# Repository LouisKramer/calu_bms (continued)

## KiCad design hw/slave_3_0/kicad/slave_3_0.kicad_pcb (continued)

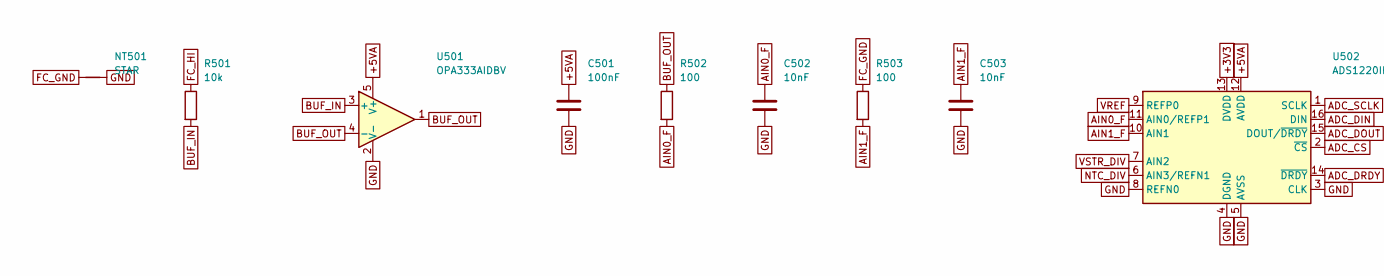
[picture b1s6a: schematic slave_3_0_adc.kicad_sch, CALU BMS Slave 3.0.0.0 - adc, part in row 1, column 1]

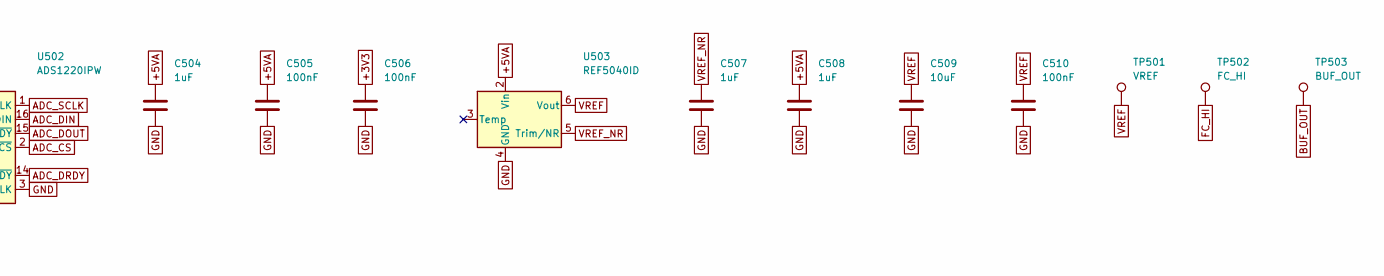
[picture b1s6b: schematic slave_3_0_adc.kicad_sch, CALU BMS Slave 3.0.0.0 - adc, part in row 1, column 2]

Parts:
C501, C505, C506: 100nF; C_0603_1608Metric
C502, C503: 10nF; C_0603_1608Metric
C504, C507, C508: 1uF; C_0603_1608Metric
C509: 10uF; C_0805_2012Metric
C510: 100nF; C_0805_2012Metric
NT501: STAR; NetTie-2_SMD_Pad0.5mm
R501: 10k; R_0603_1608Metric
R502, R503: 100; R_0603_1608Metric
TP501: VREF; TestPoint_Pad_D1.0mm
TP502: FC_HI; TestPoint_Pad_D1.0mm
TP503: BUF_OUT; TestPoint_Pad_D1.0mm
U501: OPA333AIDBV; SOT-23-5
U502: ADS1220IPW; TSSOP-16_4.4x5mm_P0.65mm
U503: REF5040ID; SOIC-8_3.9x4.9mm_P1.27mm

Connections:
+3V3: C506.1, U502.13 (DVDD); also elsewhere on the board
+5VA: C501.1, C504.1, C505.1, C508.1, U501.5 (V+), U502.12 (AVDD), U503.2 (Vin); also elsewhere on the board
ADC_CS: U502.2 (~CS); also elsewhere on the board
ADC_DIN: U502.16 (DIN); also elsewhere on the board
ADC_DOUT: U502.15 (DOUT/~DRDY); also elsewhere on the board
ADC_DRDY: U502.14 (~DRDY); also elsewhere on the board
ADC_SCLK: U502.1 (SCLK); also elsewhere on the board
AIN0_F: C502.1, R502.2, U502.11 (AIN0/REFP1)
AIN1_F: C503.1, R503.2, U502.10 (AIN1)
BUF_IN: R501.2, U501.3 (+)
BUF_OUT: R502.1, TP503.1 (1_1), U501.1, U501.4 (-)
FC_GND: NT501.1, R503.1; also elsewhere on the board
FC_HI: R501.1, TP502.1 (1_1); also elsewhere on the board
GND: C501.2, C502.2, C503.2, C504.2, C505.2, C506.2, C507.2, C508.2, C509.2, C510.2, NT501.2, U501.2 (V-), U502.3 (CLK), U502.4 (DGND), U502.5 (AVSS), U502.8 (REFN0), U503.4 (GND); also elsewhere on the board
NTC_DIV: U502.6 (AIN3/REFN1); also elsewhere on the board
VREF: C509.1, C510.1, TP501.1 (1_1), U502.9 (REFP0), U503.6 (Vout); also elsewhere on the board
VREF_NR: C507.1, U503.5 (Trim/NR)
VSTR_DIV: U502.7 (AIN2); also elsewhere on the board

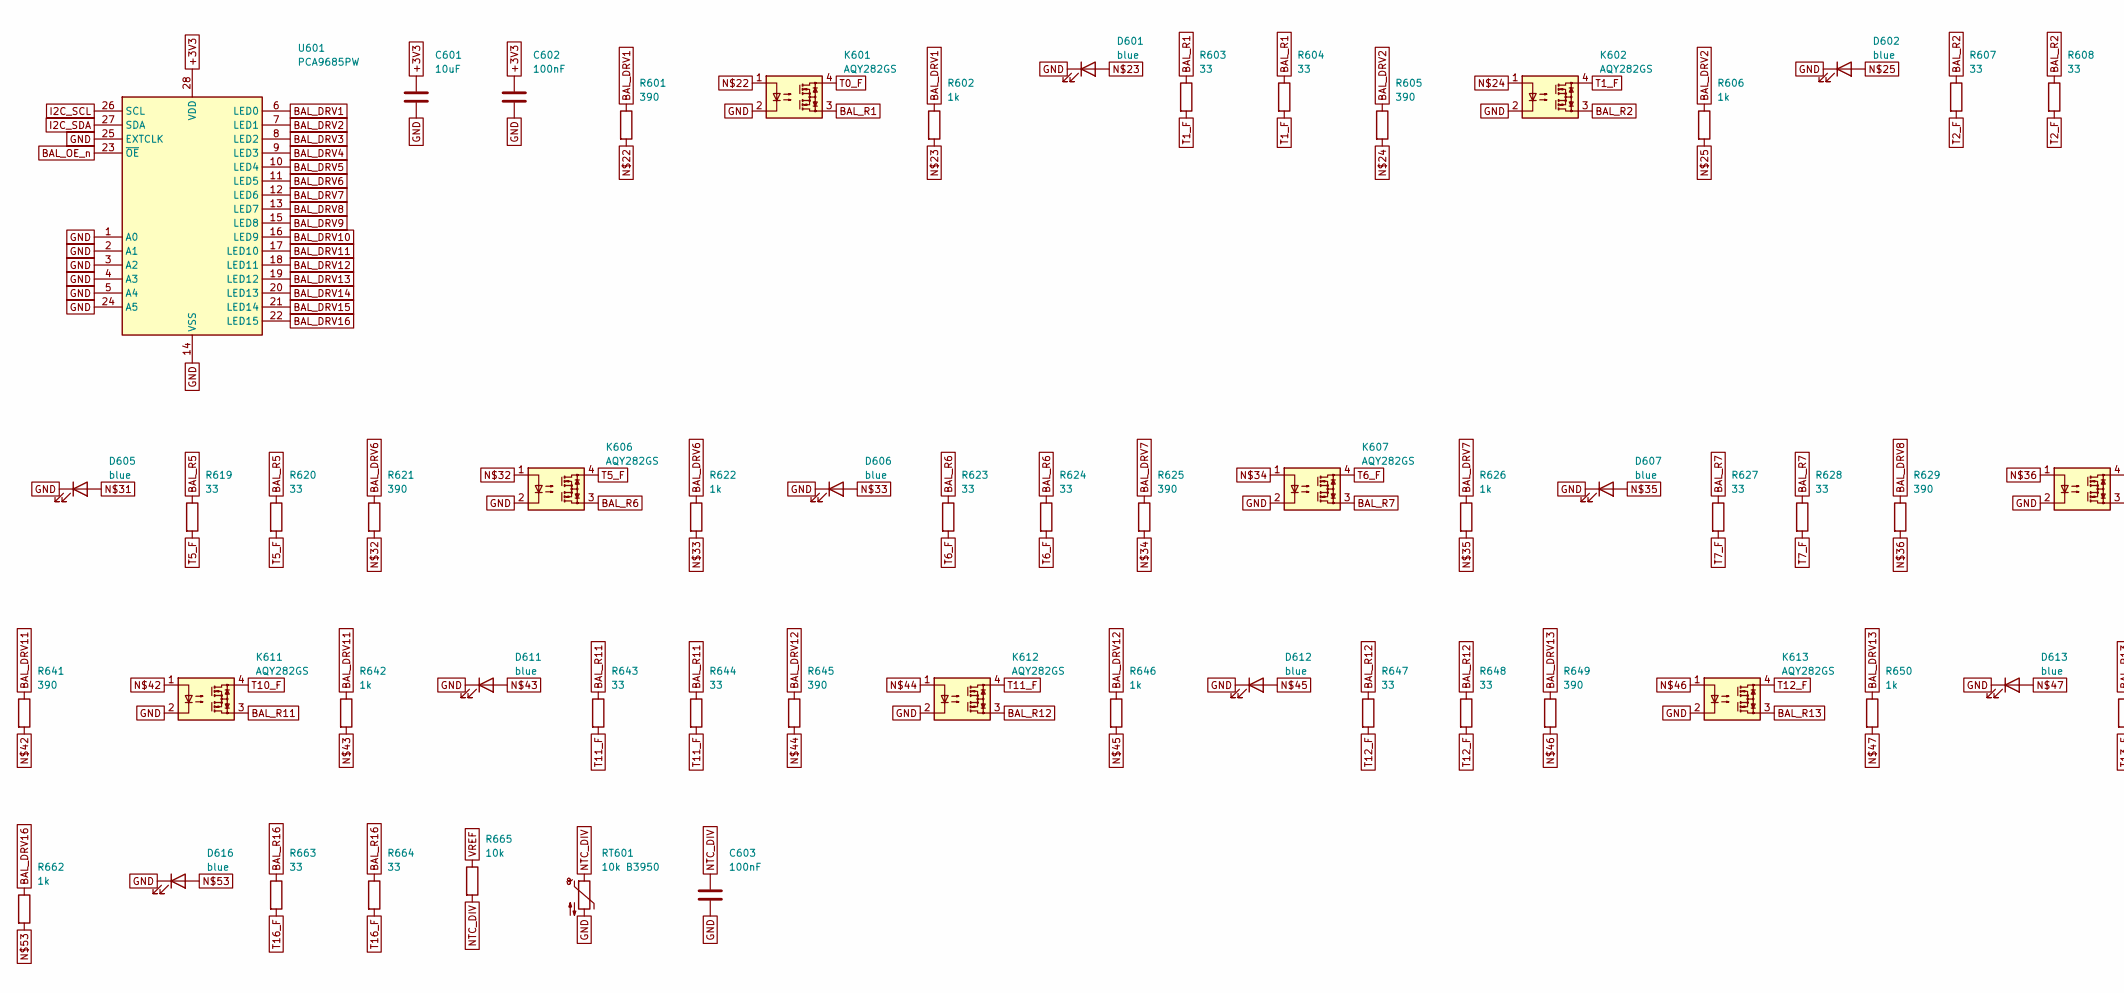
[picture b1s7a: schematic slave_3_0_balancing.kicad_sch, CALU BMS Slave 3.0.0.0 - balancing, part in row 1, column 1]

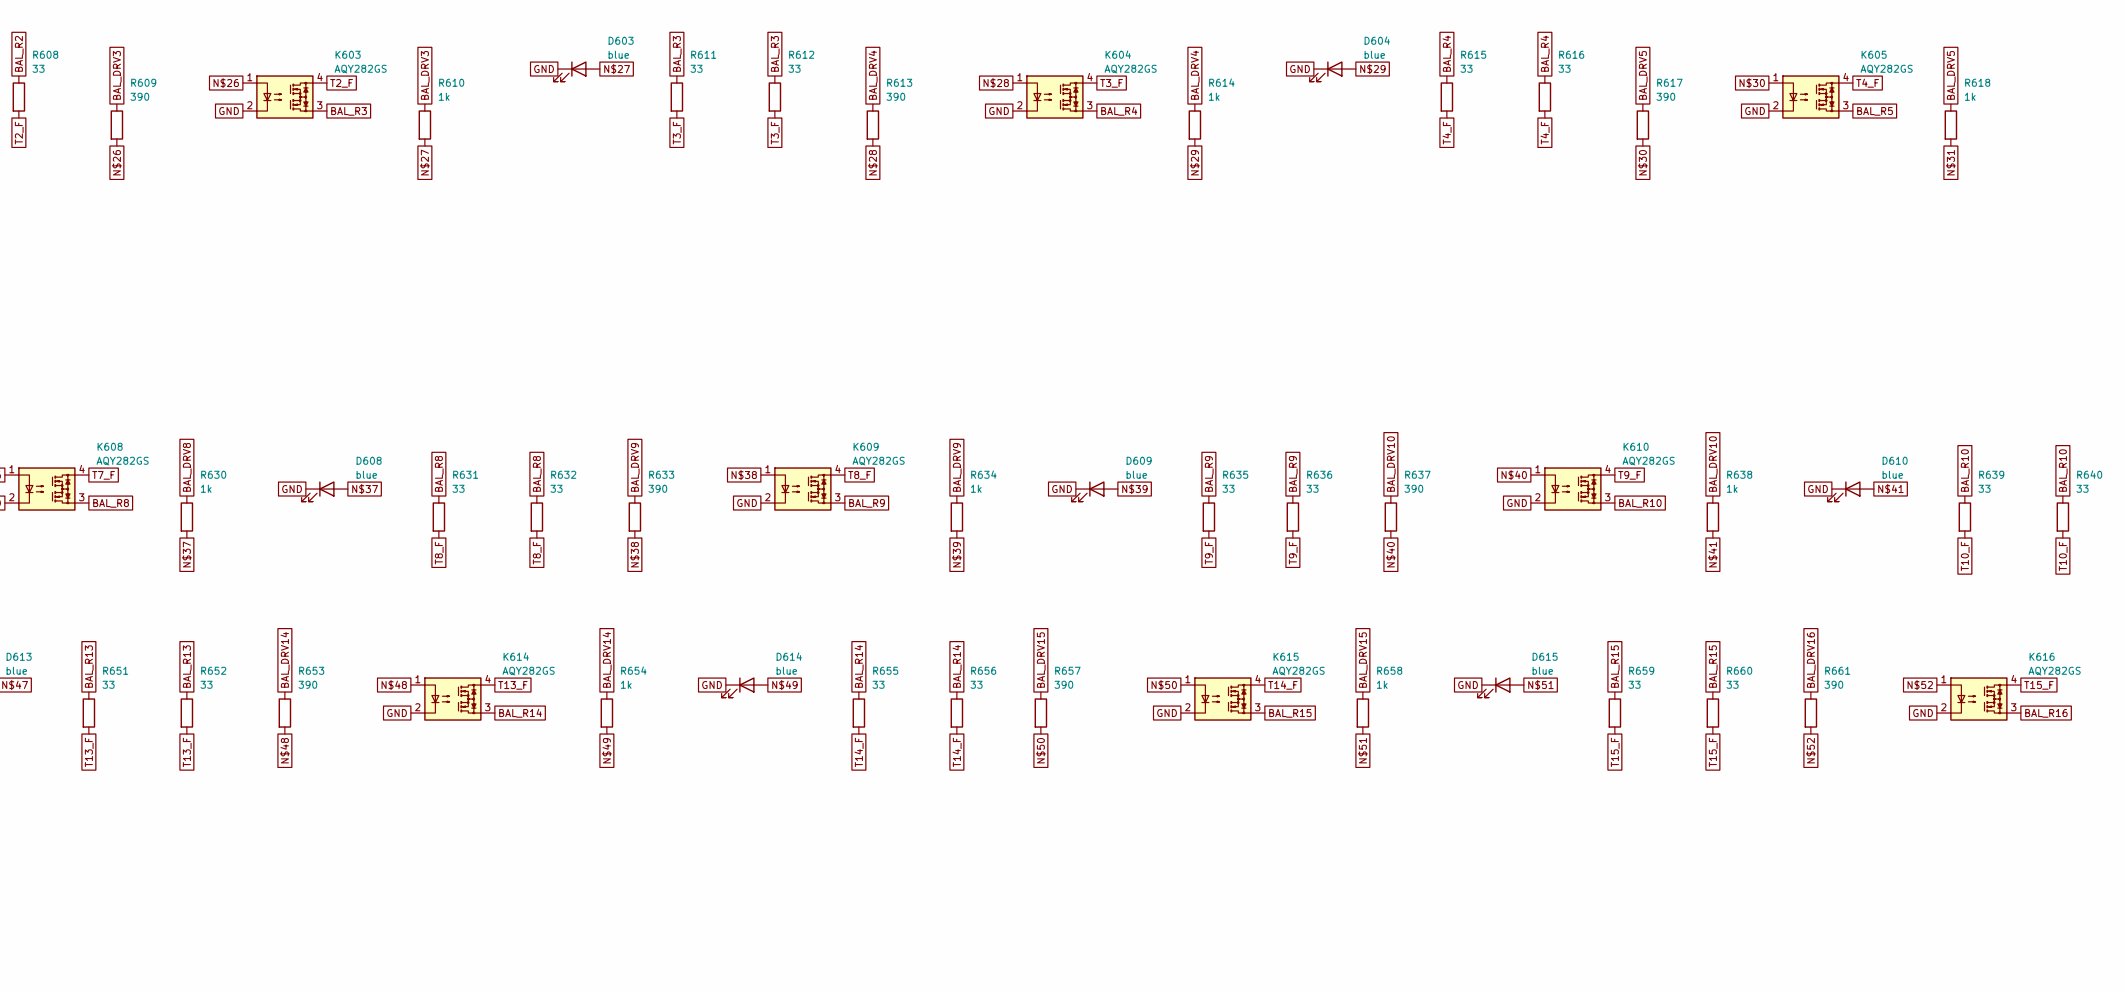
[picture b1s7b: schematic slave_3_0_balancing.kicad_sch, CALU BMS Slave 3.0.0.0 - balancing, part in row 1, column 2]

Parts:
C601: 10uF; C_0603_1608Metric
C602, C603: 100nF; C_0603_1608Metric
D601, D602, D603, D604, D605, D606, D607, D608, D609, D610, D611, D612, D613, D614, D615, D616: blue; LED_0603_1608Metric
K601, K602, K603, K604, K605, K606, K607, K608, K609, K610, K611, K612, K613, K614, K615, K616: AQY282GS; SO-4_4.4x3.9mm_P2.54mm
R601, R605, R609, R613, R617, R621, R625, R629, R633, R637, R641, R645, R649, R653, R657, R661: 390; R_0603_1608Metric
R602, R606, R610, R614, R618, R622, R626, R630, R634, R638, R642, R646, R650, R654, R658, R662: 1k; R_0603_1608Metric
R603, R604, R607, R608, R611, R612, R615, R616, R619, R620, R623, R624, R627, R628, R631, R632, R635, R636, R639, R640, R643, R644, R647, R648, R651, R652, R655, R656, R659, R660, R663, R664: 33; R_2512_6332Metric
R665: 10k; R_0603_1608Metric
RT601: 10k B3950; R_0603_1608Metric
U601: PCA9685PW; TSSOP-28_4.4x9.7mm_P0.65mm

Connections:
+3V3: C601.1, C602.1, U601.28 (VDD); also elsewhere on the board
BAL_DRV1: R601.1, R602.1, U601.6 (LED0)
BAL_DRV2: R605.1, R606.1, U601.7 (LED1)
BAL_DRV3: R609.1, R610.1, U601.8 (LED2)
BAL_DRV4: R613.1, R614.1, U601.9 (LED3)
BAL_DRV5: R617.1, R618.1, U601.10 (LED4)
BAL_DRV6: R621.1, R622.1, U601.11 (LED5)
BAL_DRV7: R625.1, R626.1, U601.12 (LED6)
BAL_DRV8: R629.1, R630.1, U601.13 (LED7)
BAL_DRV9: R633.1, R634.1, U601.15 (LED8)
BAL_DRV10: R637.1, R638.1, U601.16 (LED9)
BAL_DRV11: R641.1, R642.1, U601.17 (LED10)
BAL_DRV12: R645.1, R646.1, U601.18 (LED11)
BAL_DRV13: R649.1, R650.1, U601.19 (LED12)
BAL_DRV14: R653.1, R654.1, U601.20 (LED13)
BAL_DRV15: R657.1, R658.1, U601.21 (LED14)
BAL_DRV16: R661.1, R662.1, U601.22 (LED15)
BAL_OE_n: U601.23 (~OE); also elsewhere on the board
BAL_R1: K601.3, R603.1, R604.1
BAL_R2: K602.3, R607.1, R608.1
BAL_R3: K603.3, R611.1, R612.1
BAL_R4: K604.3, R615.1, R616.1
BAL_R5: K605.3, R619.1, R620.1
BAL_R6: K606.3, R623.1, R624.1
BAL_R7: K607.3, R627.1, R628.1
BAL_R8: K608.3, R631.1, R632.1
BAL_R9: K609.3, R635.1, R636.1
BAL_R10: K610.3, R639.1, R640.1
BAL_R11: K611.3, R643.1, R644.1
BAL_R12: K612.3, R647.1, R648.1
BAL_R13: K613.3, R651.1, R652.1
BAL_R14: K614.3, R655.1, R656.1
BAL_R15: K615.3, R659.1, R660.1
BAL_R16: K616.3, R663.1, R664.1
GND: C601.2, C602.2, C603.2, D601.1 (K), D602.1 (K), D603.1 (K), D604.1 (K), D605.1 (K), D606.1 (K), D607.1 (K), D608.1 (K), D609.1 (K), D610.1 (K), D611.1 (K), D612.1 (K), D613.1 (K), D614.1 (K), D615.1 (K), D616.1 (K), K601.2, K602.2, K603.2, K604.2, K605.2, K606.2, K607.2, K608.2, K609.2, K610.2, K611.2, K612.2, K613.2, K614.2, K615.2, K616.2, RT601.2, U601.1 (A0), U601.2 (A1), U601.3 (A2), U601.4 (A3), U601.5 (A4), U601.14 (VSS), U601.24 (A5), U601.25 (EXTCLK); also elsewhere on the board
I2C_SCL: U601.26 (SCL); also elsewhere on the board
I2C_SDA: U601.27 (SDA); also elsewhere on the board
unnamed: K601.1, R601.2
unnamed: D601.2 (A), R602.2
unnamed: K602.1, R605.2
unnamed: D602.2 (A), R606.2
unnamed: K603.1, R609.2
unnamed: D603.2 (A), R610.2
unnamed: K604.1, R613.2
unnamed: D604.2 (A), R614.2
unnamed: K605.1, R617.2
unnamed: D605.2 (A), R618.2
unnamed: K606.1, R621.2
unnamed: D606.2 (A), R622.2
unnamed: K607.1, R625.2
unnamed: D607.2 (A), R626.2
unnamed: K608.1, R629.2
unnamed: D608.2 (A), R630.2
unnamed: K609.1, R633.2
unnamed: D609.2 (A), R634.2
unnamed: K610.1, R637.2
unnamed: D610.2 (A), R638.2
unnamed: K611.1, R641.2
unnamed: D611.2 (A), R642.2
unnamed: K612.1, R645.2
unnamed: D612.2 (A), R646.2
unnamed: K613.1, R649.2
unnamed: D613.2 (A), R650.2
unnamed: K614.1, R653.2
unnamed: D614.2 (A), R654.2
unnamed: K615.1, R657.2
unnamed: D615.2 (A), R658.2
unnamed: K616.1, R661.2
unnamed: D616.2 (A), R662.2
NTC_DIV: C603.1, R665.2, RT601.1; also elsewhere on the board
T0_F: K601.4; also elsewhere on the board
T1_F: K602.4, R603.2, R604.2; also elsewhere on the board
T2_F: K603.4, R607.2, R608.2; also elsewhere on the board
T3_F: K604.4, R611.2, R612.2; also elsewhere on the board
T4_F: K605.4, R615.2, R616.2; also elsewhere on the board
T5_F: K606.4, R619.2, R620.2; also elsewhere on the board
T6_F: K607.4, R623.2, R624.2; also elsewhere on the board
T7_F: K608.4, R627.2, R628.2; also elsewhere on the board
T8_F: K609.4, R631.2, R632.2; also elsewhere on the board
T9_F: K610.4, R635.2, R636.2; also elsewhere on the board
T10_F: K611.4, R639.2, R640.2; also elsewhere on the board
T11_F: K612.4, R643.2, R644.2; also elsewhere on the board
T12_F: K613.4, R647.2, R648.2; also elsewhere on the board
T13_F: K614.4, R651.2, R652.2; also elsewhere on the board
T14_F: K615.4, R655.2, R656.2; also elsewhere on the board
T15_F: K616.4, R659.2, R660.2; also elsewhere on the board
T16_F: R663.2, R664.2; also elsewhere on the board
VREF: R665.1; also elsewhere on the board

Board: 2 copper layers, 307 parts (0 on the bottom side), 239 nets, no tracks yet.

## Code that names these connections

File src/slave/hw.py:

# hw.py - Hardware description of CALU BMS Slave HW 2.0.1.0
# Source: hw/CALU_BMS_Slave_2_0_1_0.epro2 (PCB netlist)
from micropython import const
from lib.cell_monitor import TAP_GND, TAP_B_BOT

HW_VERSION = "2.0.1.0"

# ----------------------------------------------------------------------
# GPIO
# ----------------------------------------------------------------------
PIN_SPI_SCLK = const(6)
PIN_SPI_MOSI = const(7)
PIN_SPI_MISO = const(15)   # 1k pull-up on board

PIN_DEMUX_A0 = const(16)
PIN_DEMUX_A1 = const(17)
PIN_DEMUX_A2 = const(18)
PIN_DEMUX_A3 = const(8)
PIN_DEMUX_EN = const(10)   # SN74HC154 G1, active low (no pull-up on board)

PIN_I2C_SCL = const(11)    # 1k pull-up to 3V3, PCA9685 supplied from +5V
PIN_I2C_SDA = const(3)

PIN_ONEWIRE = const(9)     # DS18B20 bus on CN2..CN5, 4.7k pull-up on board

PIN_LED_USR = const(40)    # green, active low
PIN_LED_ERR = const(39)    # red, active low

PIN_STR_SEL = (41, 42, 2, 38)  # DIP SW1 switch 1..4 = address bit 0..3, ON = 3V3 -> internal pull-down

PIN_ACT_BAL_EN = const(47)     # to external active balancer (U18/U36 pin 19), not used yet
PIN_ACT_BAL_PWM = const(48)    # U18/U36 pin 20

# ----------------------------------------------------------------------
# SPI / ADS1118
# ----------------------------------------------------------------------
SPI_BAUD = const(1_000_000)
SPI_POLARITY = const(0)    # ADS1118: SPI mode 1
SPI_PHASE = const(1)
ADS_PGA = const(2)         # +-2.048 V, all divided taps stay below ~1.94 V at 3.65 V/cell
ADS_DR = const(4)          # 128 SPS

# (demux output, tap on AIN0..AIN3, divider ratio AIN0..AIN3)
# Tap n = BAn+ (1..32), TAP_GND = BA1- (board GND), TAP_B_BOT = BA17-.
# ratio = (R_top + 10k) / 10k  ->  V_tap = V_ain * ratio
# The ratios are the E24 values chosen by main:tools/resisitor_calc.py (ideal 2*n, i.e. 2 V at
# 4 V/cell); using them directly equals applying its precalculated correction gain (ideal / actual).
#
# Every tap is measured single-ended (AINx vs GND). A differential pair such as AIN0-AIN1 is NOT
# proportional to the cell voltage, because both inputs use different ratios:
#   d = V_tap(n)/r_n - V_tap(n-1)/r_(n-1)  (0 V for two equal cells on taps 1/2)
#   V_cell(n) = r_n*d + (r_n - r_(n-1)) * V_ain(n-1)  -> needs the absolute lower input anyway.
# Chaining differentials from GND was evaluated and is worse here: 710 kOhm input impedance at
# +-0.256 V (~2.7 % error on every difference) and accumulating offsets.
ADC_MAP = (
    # string A (cells 1..16)
    (1,  (TAP_GND, 1, 3, 2),        (1.0, 2.0, 6.1, 4.0)),       # U72
    (2,  (3, 4, 6, 5),              (6.1, 8.0, 12.0, 10.1)),     # U73
    (3,  (6, 7, 9, 8),              (12.0, 14.0, 18.0, 16.0)),   # U74
    (4,  (9, 10, 12, 11),           (18.0, 20.0, 24.0, 22.0)),   # U75
    (5,  (12, 13, 15, 14),          (24.0, 26.0, 30.0, 27.0)),   # U76
    (6,  (15, 16, 16, TAP_GND),     (30.0, 32.0, 32.0, 1.0)),    # U77
    # string B (cells 17..32)
    (15, (TAP_B_BOT, 17, 19, 18),   (32.0, 33.0, 38.0, 36.0)),   # U66
    (14, (19, 20, 22, 21),          (38.0, 41.0, 45.0, 41.0)),   # U67
    (13, (22, 23, 25, 24),          (45.0, 45.0, 49.0, 49.0)),   # U68
    (12, (25, 26, 28, 27),          (49.0, 49.0, 55.0, 55.0)),   # U69
    (11, (28, 29, 31, 30),          (55.0, 55.0, 61.0, 61.0)),   # U70
    (10, (31, 32, 32, TAP_B_BOT),   (61.0, 61.0, 61.0, 32.0)),   # U71
)
NR_ADC_STRING_A = const(6)
# Above ~3.85 V/cell the BA26+ input (ratio 49) saturates -> front end is sized for LFP.

# ----------------------------------------------------------------------
# Balancing (PCA9685 -> BSS138 -> GAQY211 PhotoMOS -> 5.1R 2512 across the cell)
# ----------------------------------------------------------------------
PCA_ADDR = (0x40, 0x41)    # U5: cells 1..16, U23: cells 17..32 (channel = (cell-1) % 16)
BAL_PWM_FREQ = const(100)
BAL_RESISTOR_OHM = 5.1
BAL_RESISTOR_RATED_W = 1.0   # Yageo RC2512, without extra cooling

# ----------------------------------------------------------------------
# Cell configuration limits
# ----------------------------------------------------------------------
# The LM2596HVS-5.0 is fed from BA16+, so string A must always reach BA16+ (unused taps bridged).
# 4 cells keep >= 10 V even at 2.5 V/cell (LFP empty); the LM2596 needs >= ~7 V.
MIN_CELLS_A = const(4)

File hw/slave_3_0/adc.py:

"""Sheet ADC: zero-drift buffer, ADS1220 (24 bit, PGA bypassed) with REF5040 4.096 V reference,
string voltage and bleed-resistor NTC on AIN2/AIN3."""
from skidl import Net, subcircuit
from common import (NC, ADC_CS, ADC_DIN, ADC_DOUT, ADC_DRDY, ADC_SCLK, FC_GND, FC_HI, GND, P, P3V3, P5VA, R, C, VREF,
                    VSTR_DIV, decouple, sheet, tp, two)


@subcircuit
def adc(ntc_div):
    sheet(500)
    buf_in, buf_out, ain0, ain1 = Net("BUF_IN"), Net("BUF_OUT"), Net("AIN0_F"), Net("AIN1_F")

    # FC_GND joins GND at one point next to the ADC (net tie = star point in the layout)
    nt = P("Device", "NetTie_2", "NT", "STAR", "NetTie:NetTie-2_SMD_Pad0.5mm")
    two(nt, FC_GND, GND)

    # Unity-gain buffer, 10k limits fault current into the input clamp diodes
    two(R("10k"), FC_HI, buf_in)
    op = P("Amplifier_Operational", "OPA333xxDBV", "U", "OPA333AIDBV")
    op[3] += buf_in     # +IN
    op[4] += buf_out    # -IN
    op[1] += buf_out    # OUT
    op[5] += P5VA
    op[2] += GND
    decouple(P5VA, "100nF")

    two(R("100"), buf_out, ain0)
    two(C("10nF", note="C0G"), ain0, GND)
    two(R("100"), FC_GND, ain1)
    two(C("10nF", note="C0G"), ain1, GND)

    # ADS1220 pins: 1 SCLK, 2 ~CS, 3 CLK, 4 DGND, 5 AVSS, 6 AIN3, 7 AIN2, 8 REFN0, 9 REFP0, 10 AIN1,
    # 11 AIN0, 12 AVDD, 13 DVDD, 14 ~DRDY, 15 DOUT, 16 DIN
    u = P("Analog_ADC", "ADS1220xPW", "U", "ADS1220IPW")
    for pin, net in ((1, ADC_SCLK), (2, ADC_CS), (3, GND), (4, GND), (5, GND), (6, ntc_div), (7, VSTR_DIV),
                     (8, GND), (9, VREF), (10, ain1), (11, ain0), (12, P5VA), (13, P3V3), (14, ADC_DRDY),
                     (15, ADC_DOUT), (16, ADC_DIN)):
        u[pin] += net
    decouple(P5VA, "1uF", "100nF")
    decouple(P3V3, "100nF")

    # REF5040: 1 DNC, 2 VIN, 3 TEMP, 4 GND, 5 TRIM/NR, 6 VOUT, 7 NC, 8 DNC
    ref = P("Reference_Voltage", "REF5040ID", "U", "REF5040ID")
    nr = Net("VREF_NR")
    ref[2] += P5VA
    ref[4] += GND
    ref[5] += nr
    ref[6] += VREF
    for pin in (1, 3, 7, 8):
        ref[pin] += NC
    two(C("1uF"), nr, GND)
    decouple(P5VA, "1uF")
    decouple(VREF, "10uF", "100nF", size="0805")

    tp(VREF, "VREF")
    tp(FC_HI, "FC_HI")
    tp(buf_out, "BUF_OUT")
